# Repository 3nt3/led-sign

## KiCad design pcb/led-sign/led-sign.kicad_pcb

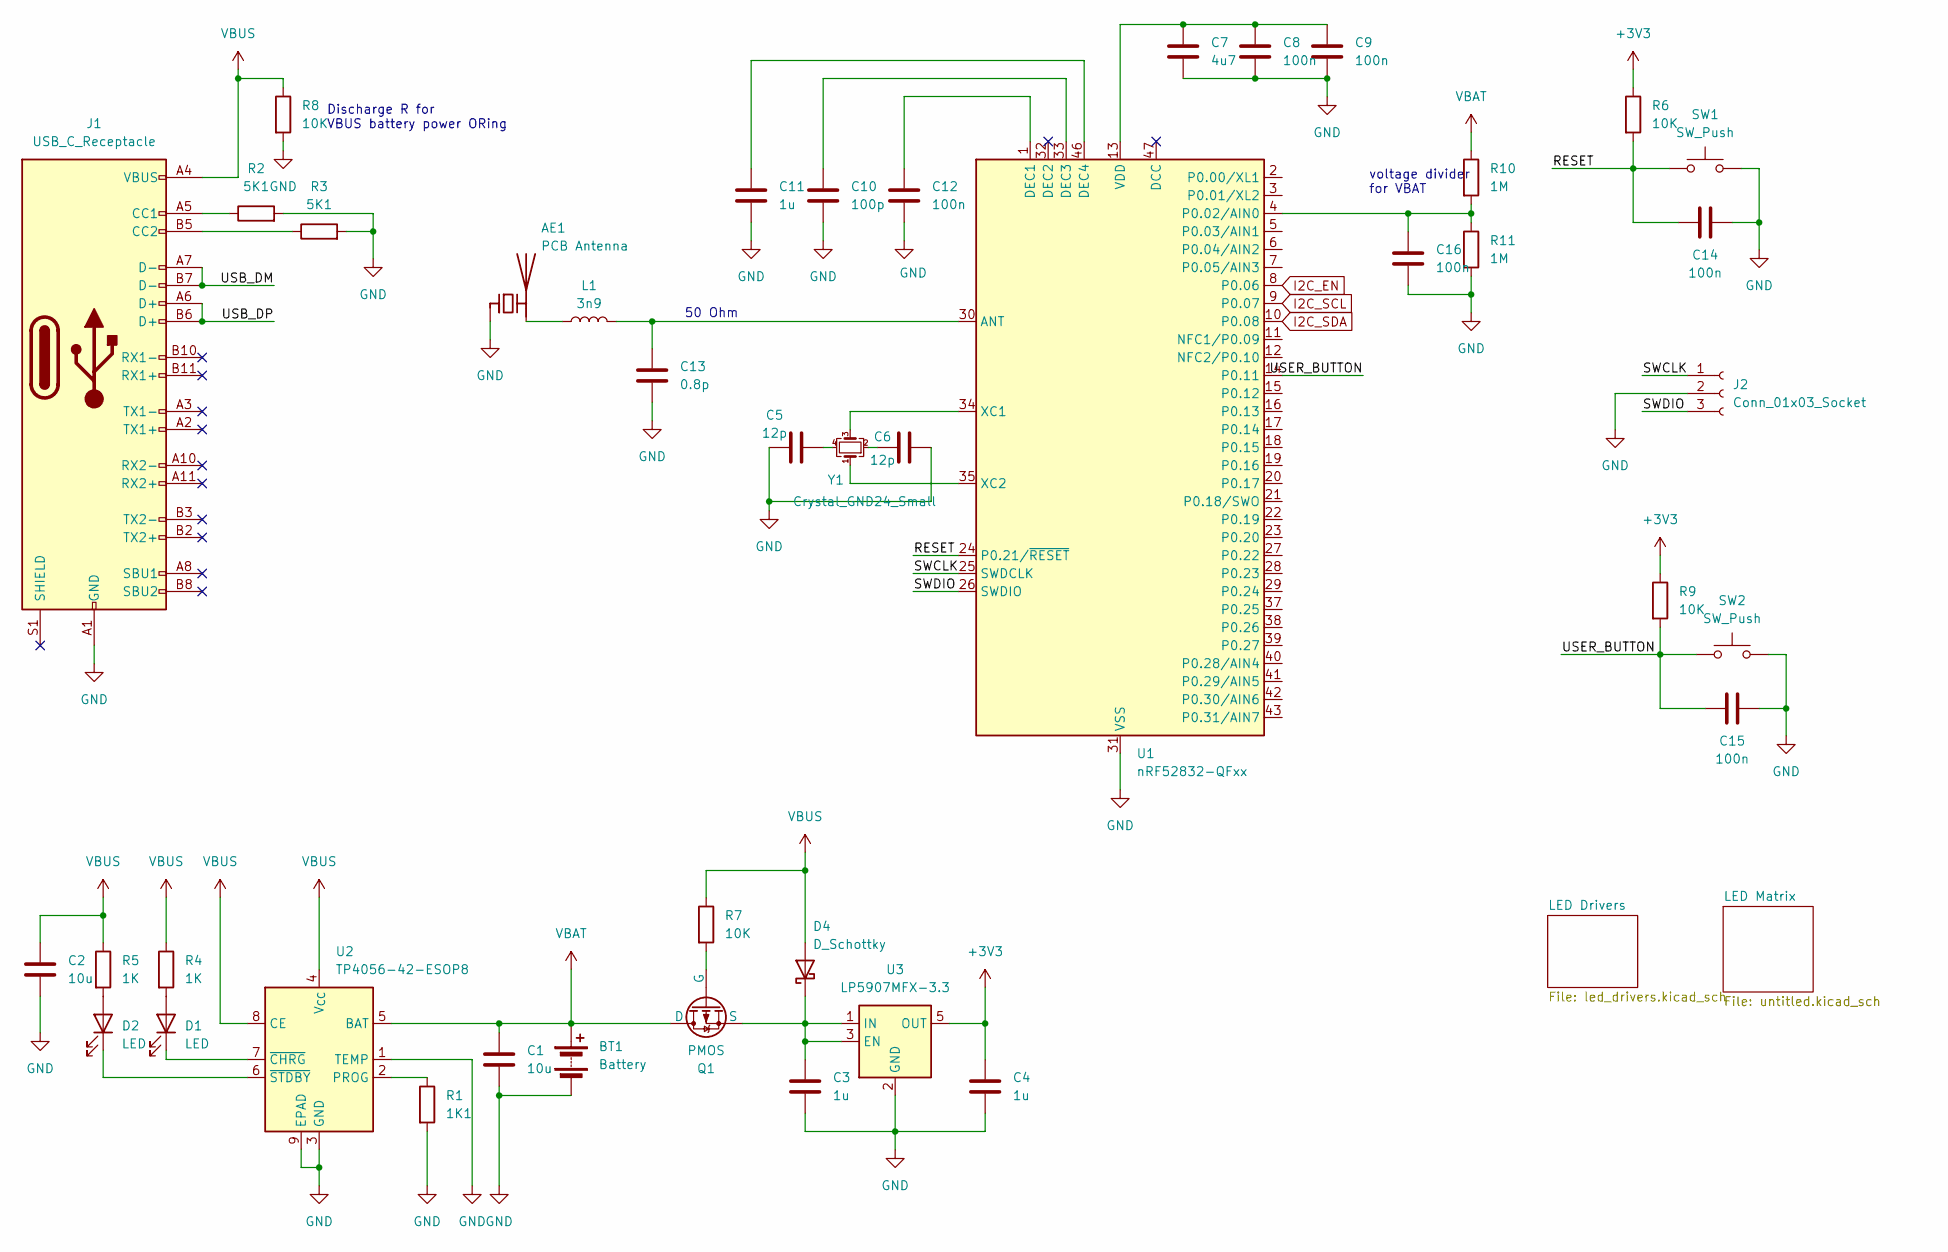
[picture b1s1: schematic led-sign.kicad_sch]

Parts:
AE1: PCB Antenna; Texas_SWRA117D_2.4GHz_Left
BT1: Battery; JST_SH_SM02B-SRSS-TB_1x02-1MP_P1.00mm_Horizontal
C1, C2: 10u; C_0603_1608Metric_Pad1.08x0.95mm_HandSolder
C3, C4, C11: 1u; C_0603_1608Metric_Pad1.08x0.95mm_HandSolder
C5, C6: 12p; C_0603_1608Metric_Pad1.08x0.95mm_HandSolder
C7: 4u7; C_0603_1608Metric_Pad1.08x0.95mm_HandSolder
C8, C9, C12, C14, C15, C16: 100n; C_0603_1608Metric_Pad1.08x0.95mm_HandSolder
C10: 100p; C_0603_1608Metric_Pad1.08x0.95mm_HandSolder
C13: 0.8p; C_0603_1608Metric_Pad1.08x0.95mm_HandSolder
D1, D2: LED; LED_0603_1608Metric_Pad1.05x0.95mm_HandSolder_Triangle
D4: D_Schottky; D_0603_1608Metric_Pad1.05x0.95mm_HandSolder
J1: USB_C_Receptacle; USB-C-SMD_MC-311D
J2: Conn_01x03_Socket; JST_SH_SM03B-SRSS-TB_1x03-1MP_P1.00mm_Horizontal
L1: 3n9; L_0603_1608Metric_Pad1.05x0.95mm_HandSolder
Q1: PMOS; SOT-23_Handsoldering
R1: 1K1; R_0603_1608Metric_Pad0.98x0.95mm_HandSolder
R2, R3: 5K1; R_0603_1608Metric_Pad0.98x0.95mm_HandSolder
R4, R5: 1K; R_0603_1608Metric_Pad0.98x0.95mm_HandSolder
R6, R7, R8, R9: 10K; R_0603_1608Metric_Pad0.98x0.95mm_HandSolder
R10, R11: 1M; R_0603_1608Metric_Pad0.98x0.95mm_HandSolder
SW1, SW2: SW_Push; SW-SMD_4P-L5.1-W5.1-P3.70-LS6.5-TL_H1.5
U1: nRF52832-QFxx; QFN-48-1EP_6x6mm_P0.4mm_EP4.6x4.6mm
U2: TP4056-42-ESOP8; SOIC-8-1EP_3.9x4.9mm_P1.27mm_EP2.41x3.3mm_ThermalVias
U3: LP5907MFX-3.3; SOT-23-5
Y1: Crystal_GND24_Small; Crystal_SMD_3225-4Pin_3.2x2.5mm

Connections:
+3V3: C4.1, R6.1, R9.1, U3.5 (OUT); also elsewhere on the board
/RESET: C14.1, R6.2, SW1.1, U1.24 (P0.21/~RESET)
/SWCLK: J2.1, U1.25 (SWDCLK)
/SWDIO: J2.3, U1.26 (SWDIO)
/USB_DM: J1.A7 (D-), J1.B7 (D-)
/USB_DP: J1.A6 (D+), J1.B6 (D+)
/USER_BUTTON: C15.1, R9.2, SW2.1, U1.14 (P0.11)
GND: AE1.1 (FEED), BT1.2 (-), C1.2, C2.2, C3.2, C4.2, C5.1, C6.2, C7.2, C8.2, C9.2, C10.2, C11.2, C12.2, C13.2, C14.2, C15.2, C16.2, J1.A1 (GND), J1.A12 (GND), J1.B1 (GND), J1.B12 (GND), J2.2, R1.2, R2.2, R3.2, R8.2, R11.2, SW1.2, SW2.2, U1.31 (VSS), U1.45 (VSS), U1.49 (VSS), U2.1 (TEMP), U2.3 (GND), U2.9 (EPAD), U3.2 (GND); also elsewhere on the board
I2C_EN: U1.8 (P0.06); also elsewhere on the board
I2C_SCL: U1.9 (P0.07); also elsewhere on the board
I2C_SDA: U1.10 (P0.08); also elsewhere on the board
unnamed: AE1.2 (PCB_Trace), L1.1
unnamed: C5.2, Y1.4
unnamed: C6.1, Y1.2
unnamed: C7.1, C8.1, C9.1, U1.13 (VDD), U1.36 (VDD), U1.48 (VDD)
unnamed: D1.2 (A), R4.2
unnamed: D1.1 (K), U2.7 (~CHRG)
unnamed: D2.2 (A), R5.2
unnamed: D2.1 (K), U2.6 (~STDBY)
unnamed: C3.1, D4.1 (K), Q1.3 (S), U3.1 (IN), U3.3 (EN)
unnamed: J1.A5 (CC1), R2.1
unnamed: J1.B5 (CC2), R3.1
unnamed: Q1.2 (G), R7.2
unnamed: C13.1, L1.2, U1.30 (ANT)
unnamed: C12.1, U1.1 (DEC1)
unnamed: C10.1, U1.33 (DEC3)
unnamed: C11.1, U1.46 (DEC4)
unnamed: C16.1, R10.2, R11.1, U1.4 (P0.02/AIN0)
unnamed: U1.34 (XC1), Y1.3
unnamed: U1.35 (XC2), Y1.1
unnamed: R1.1, U2.2 (PROG)
VBAT: BT1.1 (+), C1.1, Q1.1 (D), R10.1, U2.5 (BAT)
VBUS: C2.1, D4.2 (A), J1.A4 (VBUS), J1.A9 (VBUS), J1.B4 (VBUS), J1.B9 (VBUS), R4.1, R5.1, R7.1, R8.1, U2.4 (V_{CC}), U2.8 (CE)

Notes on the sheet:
Discharge R for VBUS battery power ORing
voltage divider for VBAT
50 Ohm

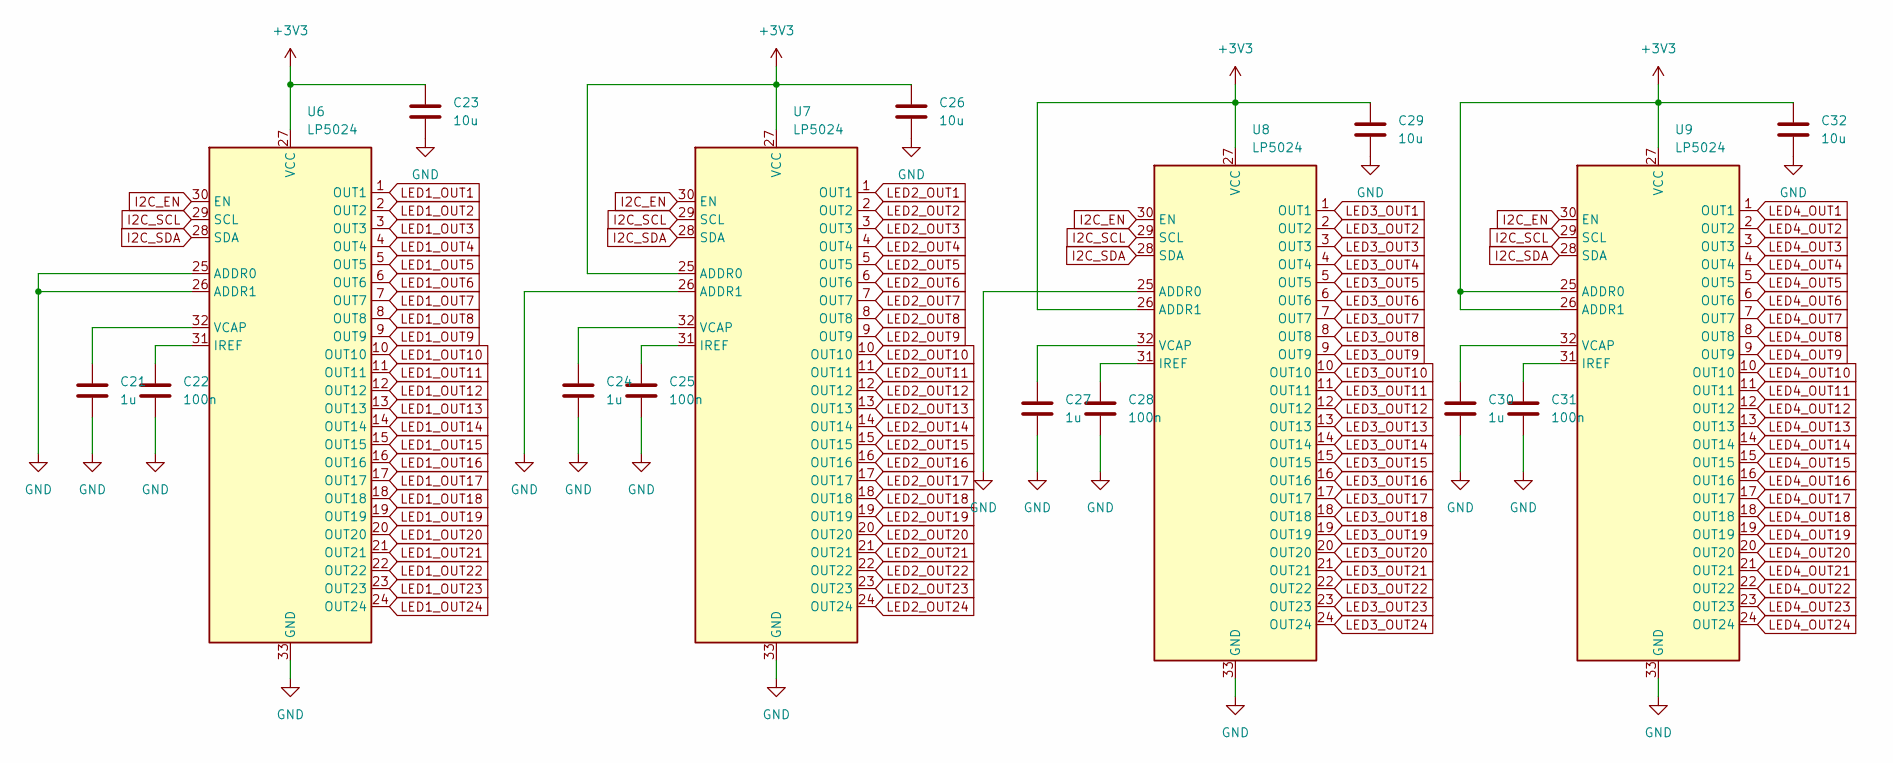
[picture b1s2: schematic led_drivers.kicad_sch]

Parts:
C21, C24, C27, C30: 1u; C_0603_1608Metric_Pad1.08x0.95mm_HandSolder
C22, C25, C28, C31: 100n; C_0603_1608Metric_Pad1.08x0.95mm_HandSolder
C23, C26, C29, C32: 10u; C_0603_1608Metric_Pad1.08x0.95mm_HandSolder
U6, U7, U8, U9: LP5024

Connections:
+3V3: C23.1, C26.1, C29.1, C32.1, U6.27 (VCC), U7.25 (ADDR0), U7.27 (VCC), U8.26 (ADDR1), U8.27 (VCC), U9.25 (ADDR0), U9.26 (ADDR1), U9.27 (VCC); also elsewhere on the board
GND: C21.2, C22.2, C23.2, C24.2, C25.2, C26.2, C27.2, C28.2, C29.2, C30.2, C31.2, C32.2, U6.25 (ADDR0), U6.26 (ADDR1), U6.33 (GND), U7.26 (ADDR1), U7.33 (GND), U8.25 (ADDR0), U8.33 (GND), U9.33 (GND); also elsewhere on the board
I2C_EN: U6.30 (EN), U7.30 (EN), U8.30 (EN), U9.30 (EN); also elsewhere on the board
I2C_SCL: U6.29 (SCL), U7.29 (SCL), U8.29 (SCL), U9.29 (SCL); also elsewhere on the board
I2C_SDA: U6.28 (SDA), U7.28 (SDA), U8.28 (SDA), U9.28 (SDA); also elsewhere on the board
LED1_OUT1: U6.1 (OUT1)
LED1_OUT2: U6.2 (OUT2)
LED1_OUT3: U6.3 (OUT3)
LED1_OUT4: U6.4 (OUT4)
LED1_OUT5: U6.5 (OUT5)
LED1_OUT6: U6.6 (OUT6)
LED1_OUT7: U6.7 (OUT7)
LED1_OUT8: U6.8 (OUT8)
LED1_OUT9: U6.9 (OUT9)
LED1_OUT10: U6.10 (OUT10)
LED1_OUT11: U6.11 (OUT11)
LED1_OUT12: U6.12 (OUT12)
LED1_OUT13: U6.13 (OUT13)
LED1_OUT14: U6.14 (OUT14)
LED1_OUT15: U6.15 (OUT15)
LED1_OUT16: U6.16 (OUT16)
LED1_OUT17: U6.17 (OUT17)
LED1_OUT18: U6.18 (OUT18)
LED1_OUT19: U6.19 (OUT19)
LED1_OUT20: U6.20 (OUT20)
LED1_OUT21: U6.21 (OUT21)
LED1_OUT22: U6.22 (OUT22)
LED1_OUT23: U6.23 (OUT23)
LED1_OUT24: U6.24 (OUT24)
LED2_OUT1: U7.1 (OUT1)
LED2_OUT2: U7.2 (OUT2)
LED2_OUT3: U7.3 (OUT3)
LED2_OUT4: U7.4 (OUT4)
LED2_OUT5: U7.5 (OUT5)
LED2_OUT6: U7.6 (OUT6)
LED2_OUT7: U7.7 (OUT7)
LED2_OUT8: U7.8 (OUT8)
LED2_OUT9: U7.9 (OUT9)
LED2_OUT10: U7.10 (OUT10)
LED2_OUT11: U7.11 (OUT11)
LED2_OUT12: U7.12 (OUT12)
LED2_OUT13: U7.13 (OUT13)
LED2_OUT14: U7.14 (OUT14)
LED2_OUT15: U7.15 (OUT15)
LED2_OUT16: U7.16 (OUT16)
LED2_OUT17: U7.17 (OUT17)
LED2_OUT18: U7.18 (OUT18)
LED2_OUT19: U7.19 (OUT19)
LED2_OUT20: U7.20 (OUT20)
LED2_OUT21: U7.21 (OUT21)
LED2_OUT22: U7.22 (OUT22)
LED2_OUT23: U7.23 (OUT23)
LED2_OUT24: U7.24 (OUT24)
LED3_OUT1: U8.1 (OUT1)
LED3_OUT2: U8.2 (OUT2)
LED3_OUT3: U8.3 (OUT3)
LED3_OUT4: U8.4 (OUT4)
LED3_OUT5: U8.5 (OUT5)
LED3_OUT6: U8.6 (OUT6)
LED3_OUT7: U8.7 (OUT7)
LED3_OUT8: U8.8 (OUT8)
LED3_OUT9: U8.9 (OUT9)
LED3_OUT10: U8.10 (OUT10)
LED3_OUT11: U8.11 (OUT11)
LED3_OUT12: U8.12 (OUT12)
LED3_OUT13: U8.13 (OUT13)
LED3_OUT14: U8.14 (OUT14)
LED3_OUT15: U8.15 (OUT15)
LED3_OUT16: U8.16 (OUT16)
LED3_OUT17: U8.17 (OUT17)
LED3_OUT18: U8.18 (OUT18)
LED3_OUT19: U8.19 (OUT19)
LED3_OUT20: U8.20 (OUT20)
LED3_OUT21: U8.21 (OUT21)
LED3_OUT22: U8.22 (OUT22)
LED3_OUT23: U8.23 (OUT23)
LED3_OUT24: U8.24 (OUT24)
LED4_OUT1: U9.1 (OUT1)
LED4_OUT2: U9.2 (OUT2)
LED4_OUT3: U9.3 (OUT3)
LED4_OUT4: U9.4 (OUT4)
LED4_OUT5: U9.5 (OUT5)
LED4_OUT6: U9.6 (OUT6)
LED4_OUT7: U9.7 (OUT7)
LED4_OUT8: U9.8 (OUT8)
LED4_OUT9: U9.9 (OUT9)
LED4_OUT10: U9.10 (OUT10)
LED4_OUT11: U9.11 (OUT11)
LED4_OUT12: U9.12 (OUT12)
LED4_OUT13: U9.13 (OUT13)
LED4_OUT14: U9.14 (OUT14)
LED4_OUT15: U9.15 (OUT15)
LED4_OUT16: U9.16 (OUT16)
LED4_OUT17: U9.17 (OUT17)
LED4_OUT18: U9.18 (OUT18)
LED4_OUT19: U9.19 (OUT19)
LED4_OUT20: U9.20 (OUT20)
LED4_OUT21: U9.21 (OUT21)
LED4_OUT22: U9.22 (OUT22)
LED4_OUT23: U9.23 (OUT23)
LED4_OUT24: U9.24 (OUT24)
unnamed: C22.1, U6.31 (IREF)
unnamed: C21.1, U6.32 (VCAP)
unnamed: C25.1, U7.31 (IREF)
unnamed: C24.1, U7.32 (VCAP)
unnamed: C28.1, U8.31 (IREF)
unnamed: C27.1, U8.32 (VCAP)
unnamed: C31.1, U9.31 (IREF)
unnamed: C30.1, U9.32 (VCAP)

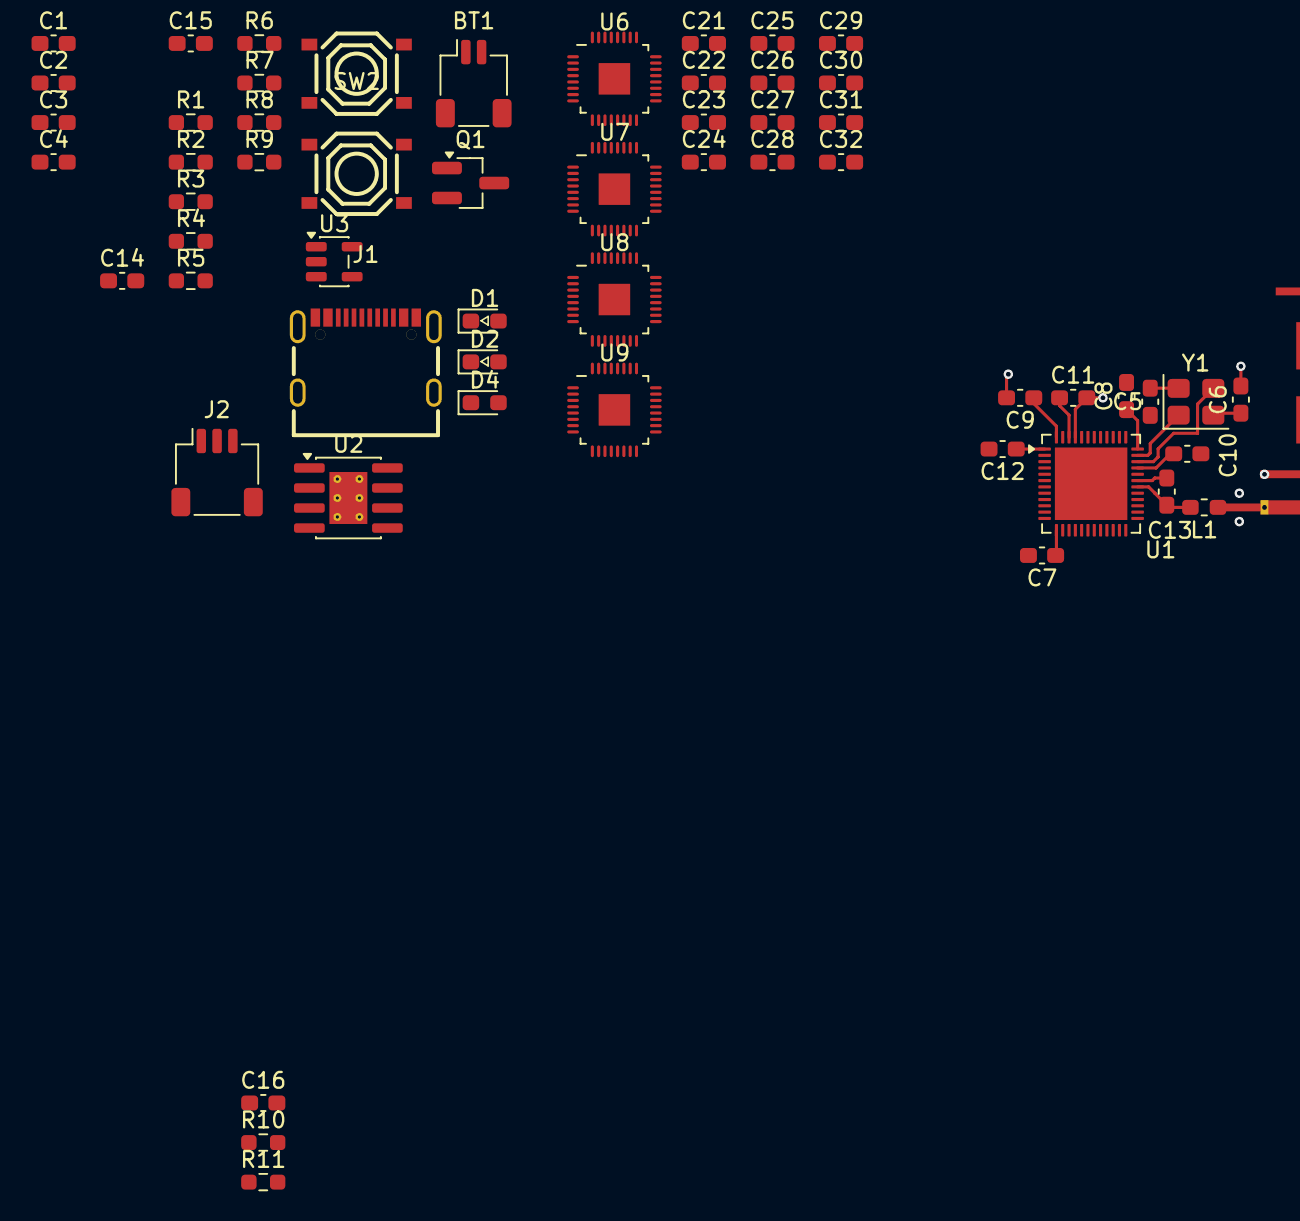
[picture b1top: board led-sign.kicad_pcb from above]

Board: 2 copper layers, 58 parts (0 on the bottom side), 41 nets.

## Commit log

2026-01-04 add led matrix
2026-01-04 start layout
